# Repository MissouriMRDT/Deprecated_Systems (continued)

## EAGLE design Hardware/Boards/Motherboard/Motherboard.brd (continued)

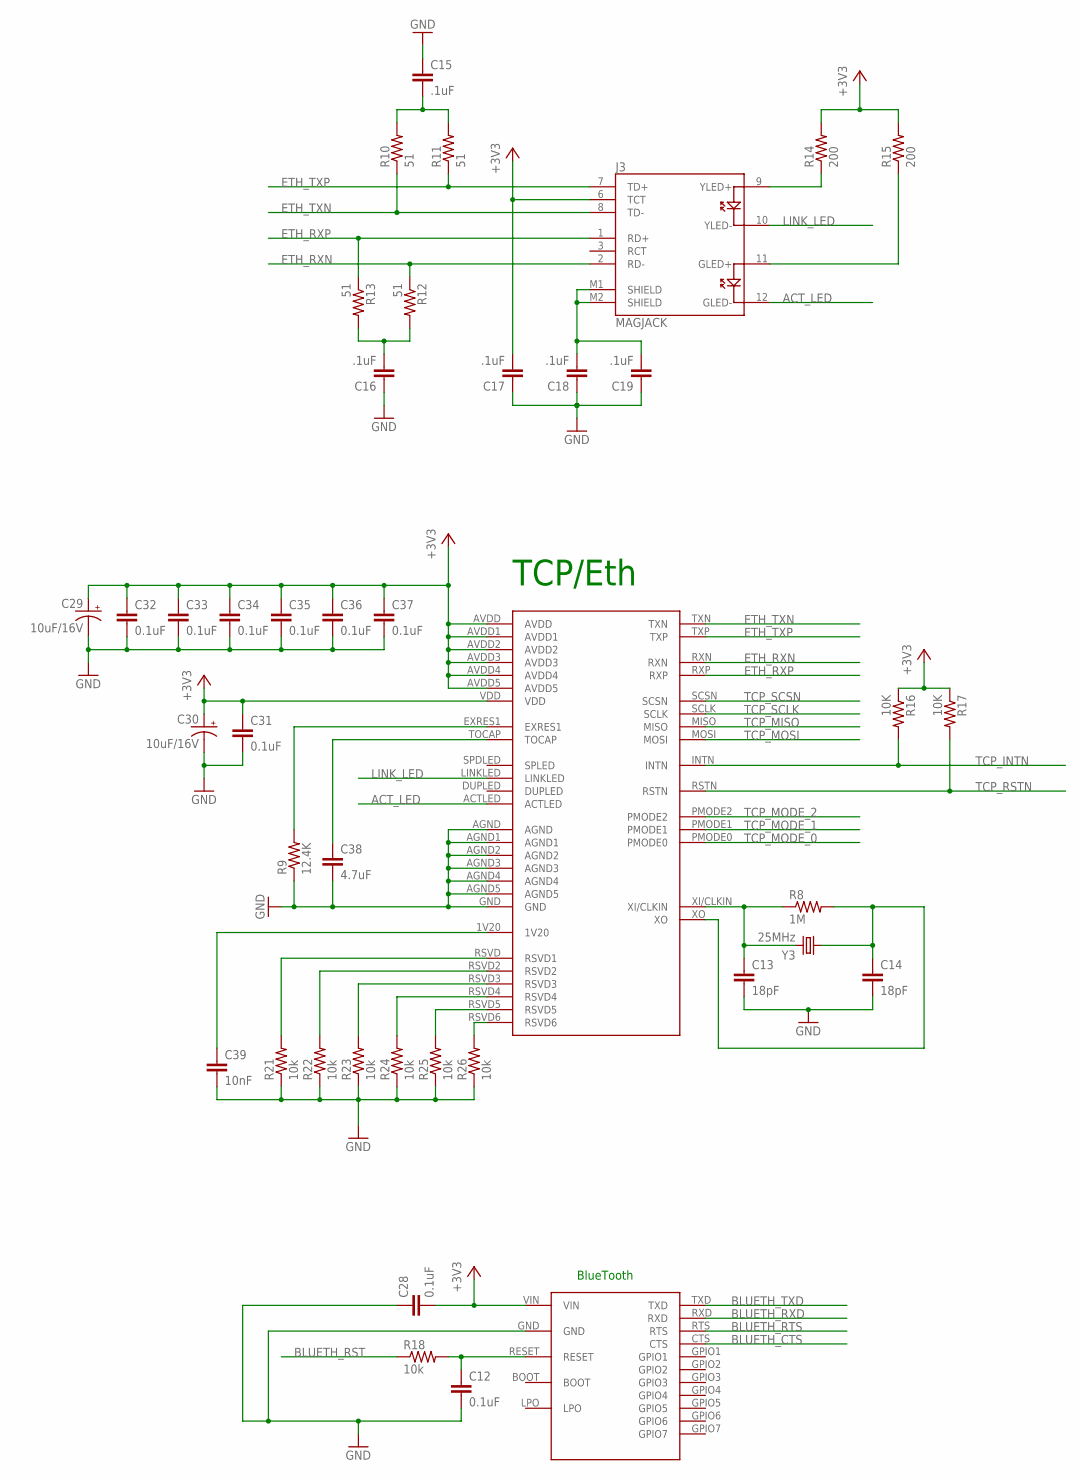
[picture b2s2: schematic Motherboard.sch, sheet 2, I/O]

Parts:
BLUETOOTH: SPBT2632C2A
C12, C28, C31, C32, C33, C34, C35, C36, C37: 0.1uF; 1206
C13, C14: 18pF; 1206
C15, C16, C17, C18, C19: .1uF; 1206
C29, C30: 10uF/16V; EIA3216
C38: 4.7uF; 1206
C39: 10nF; 1206
J3: MAGJACK
R8: 1M; 1206
R9: 12.4K; 1206
R10, R11, R12, R13: 51; 1206
R14, R15: 200; 1206
R16, R17: 10K; 1206
R18, R21, R22, R23, R24, R25, R26: 10k; 1206
U$11: W5500
Y3: 25MHz; HC49US

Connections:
+3V3: BLUETOOTH.VIN, C17.2, C28.2, C29.A (+), C30.A (+), C31.1, C32.1, C33.1, C34.1, C35.1, C36.1, C37.1, J3.6 (TCT), R14.2, R15.2, R16.1, R17.1, U$11.AVDD, U$11.AVDD1, U$11.AVDD2, U$11.AVDD3, U$11.AVDD4, U$11.AVDD5, U$11.VDD; also elsewhere on the board
ACT_LED: J3.12 (GLED-), U$11.ACTLED
BLUETH_CTS: BLUETOOTH.CTS; also elsewhere on the board
BLUETH_RST: R18.1; also elsewhere on the board
BLUETH_RTS: BLUETOOTH.RTS; also elsewhere on the board
BLUETH_RXD: BLUETOOTH.RXD; also elsewhere on the board
BLUETH_TXD: BLUETOOTH.TXD; also elsewhere on the board
ETH_RXN: J3.2 (RD-), R12.1, U$11.RXN
ETH_RXP: J3.1 (RD+), R13.1, U$11.RXP
ETH_TXN: J3.8 (TD-), R10.1, U$11.TXN
ETH_TXP: J3.7 (TD+), R11.1, U$11.TXP
GND: BLUETOOTH.GND, C12.2, C13.2, C14.2, C15.1, C16.1, C17.1, C18.1, C19.1, C28.1, C29.C (-), C30.C (-), C31.2, C32.2, C33.2, C34.2, C35.2, C36.2, C37.2, C38.2, C39.2, R9.1, R21.1, R22.1, R23.1, R24.1, R25.1, R26.1, U$11.AGND, U$11.AGND1, U$11.AGND2, U$11.AGND3, U$11.AGND4, U$11.AGND5, U$11.GND; also elsewhere on the board
LINK_LED: J3.10 (YLED-), U$11.LINKLED
unnamed: C13.1, R8.1, U$11.XI/CLKIN, Y3.2
unnamed: R9.2, U$11.EXRES1
unnamed: C14.1, R8.2, U$11.XO, Y3.1
unnamed: C15.2, R10.2, R11.2
unnamed: C16.2, R12.2, R13.2
unnamed: J3.9 (YLED+), R14.1
unnamed: C18.2, C19.2, J3.M1 (SHIELD), J3.M2 (SHIELD)
unnamed: J3.11 (GLED+), R15.1
unnamed: C38.1, U$11.TOCAP
unnamed: R26.2, U$11.RSVD6
unnamed: R25.2, U$11.RSVD5
unnamed: R24.2, U$11.RSVD4
unnamed: R23.2, U$11.RSVD3
unnamed: R22.2, U$11.RSVD2
unnamed: R21.2, U$11.RSVD (RSVD1)
unnamed: C39.1, U$11.1V20
unnamed: BLUETOOTH.RESET, C12.1, R18.2
TCP_INTN: R16.2, U$11.INTN; also elsewhere on the board
TCP_MISO: U$11.MISO; also elsewhere on the board
TCP_MODE_0: U$11.PMODE0; also elsewhere on the board
TCP_MODE_1: U$11.PMODE1; also elsewhere on the board
TCP_MODE_2: U$11.PMODE2; also elsewhere on the board
TCP_MOSI: U$11.MOSI; also elsewhere on the board
TCP_RSTN: R17.2, U$11.RSTN; also elsewhere on the board
TCP_SCLK: U$11.SCLK; also elsewhere on the board
TCP_SCSN: U$11.SCSN; also elsewhere on the board

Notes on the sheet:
TCP/Eth
BlueTooth

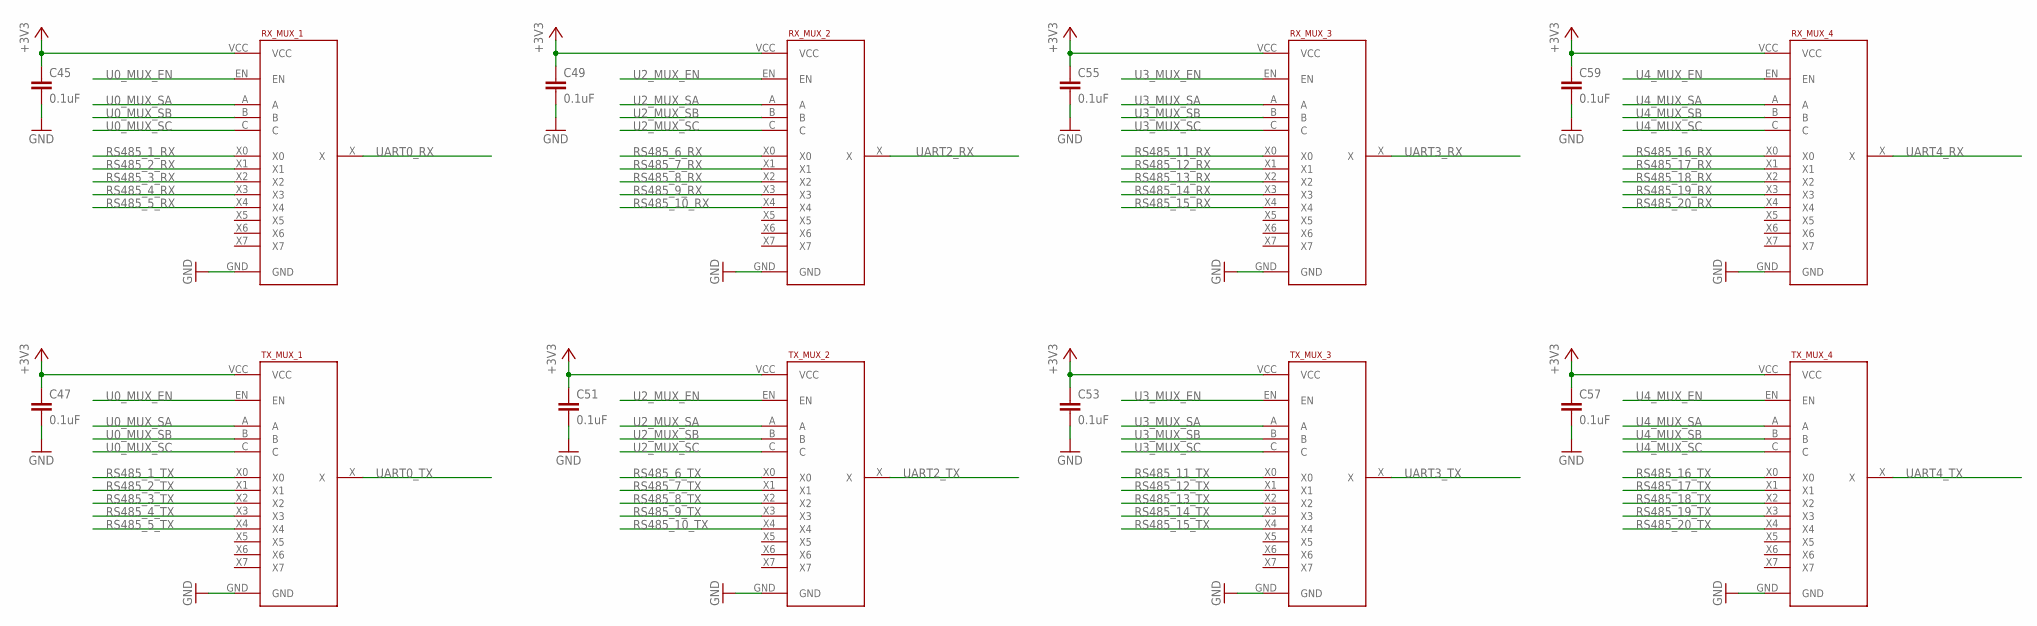
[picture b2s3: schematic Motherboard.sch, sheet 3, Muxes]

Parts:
C45, C47, C49, C51, C53, C55, C57, C59: 0.1uF; 1206
RX_MUX_1, RX_MUX_2, RX_MUX_3, RX_MUX_4: 8:1 Mux; SOIC16N
TX_MUX_1, TX_MUX_2, TX_MUX_3, TX_MUX_4: 8:1 Mux; SOIC16N

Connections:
+3V3: C45.1, C47.1, C49.1, C51.1, C53.1, C55.1, C57.1, C59.1, RX_MUX_1.VCC, RX_MUX_2.VCC, RX_MUX_3.VCC, RX_MUX_4.VCC, TX_MUX_1.VCC, TX_MUX_2.VCC, TX_MUX_3.VCC, TX_MUX_4.VCC; also elsewhere on the board
GND: C45.2, C47.2, C49.2, C51.2, C53.2, C55.2, C57.2, C59.2, RX_MUX_1.GND, RX_MUX_2.GND, RX_MUX_3.GND, RX_MUX_4.GND, TX_MUX_1.GND, TX_MUX_2.GND, TX_MUX_3.GND, TX_MUX_4.GND; also elsewhere on the board
RS485_1_RX: RX_MUX_1.X0; also elsewhere on the board
RS485_1_TX: TX_MUX_1.X0; also elsewhere on the board
RS485_2_RX: RX_MUX_1.X1; also elsewhere on the board
RS485_2_TX: TX_MUX_1.X1; also elsewhere on the board
RS485_3_RX: RX_MUX_1.X2; also elsewhere on the board
RS485_3_TX: TX_MUX_1.X2; also elsewhere on the board
RS485_4_RX: RX_MUX_1.X3; also elsewhere on the board
RS485_4_TX: TX_MUX_1.X3; also elsewhere on the board
RS485_5_RX: RX_MUX_1.X4; also elsewhere on the board
RS485_5_TX: TX_MUX_1.X4; also elsewhere on the board
RS485_6_RX: RX_MUX_2.X0; also elsewhere on the board
RS485_6_TX: TX_MUX_2.X0; also elsewhere on the board
RS485_7_RX: RX_MUX_2.X1; also elsewhere on the board
RS485_7_TX: TX_MUX_2.X1; also elsewhere on the board
RS485_8_RX: RX_MUX_2.X2; also elsewhere on the board
RS485_8_TX: TX_MUX_2.X2; also elsewhere on the board
RS485_9_RX: RX_MUX_2.X3; also elsewhere on the board
RS485_9_TX: TX_MUX_2.X3; also elsewhere on the board
RS485_10_RX: RX_MUX_2.X4; also elsewhere on the board
RS485_10_TX: TX_MUX_2.X4; also elsewhere on the board
RS485_11_RX: RX_MUX_3.X0; also elsewhere on the board
RS485_11_TX: TX_MUX_3.X0; also elsewhere on the board
RS485_12_RX: RX_MUX_3.X1; also elsewhere on the board
RS485_12_TX: TX_MUX_3.X1; also elsewhere on the board
RS485_13_RX: RX_MUX_3.X2; also elsewhere on the board
RS485_13_TX: TX_MUX_3.X2; also elsewhere on the board
RS485_14_RX: RX_MUX_3.X3; also elsewhere on the board
RS485_14_TX: TX_MUX_3.X3; also elsewhere on the board
RS485_15_RX: RX_MUX_3.X4; also elsewhere on the board
RS485_15_TX: TX_MUX_3.X4; also elsewhere on the board
RS485_16_RX: RX_MUX_4.X0; also elsewhere on the board
RS485_16_TX: TX_MUX_4.X0; also elsewhere on the board
RS485_17_RX: RX_MUX_4.X1; also elsewhere on the board
RS485_17_TX: TX_MUX_4.X1; also elsewhere on the board
RS485_18_RX: RX_MUX_4.X2; also elsewhere on the board
RS485_18_TX: TX_MUX_4.X2; also elsewhere on the board
RS485_19_RX: RX_MUX_4.X3; also elsewhere on the board
RS485_19_TX: TX_MUX_4.X3; also elsewhere on the board
RS485_20_RX: RX_MUX_4.X4; also elsewhere on the board
RS485_20_TX: TX_MUX_4.X4; also elsewhere on the board
U0_MUX_EN: RX_MUX_1.EN, TX_MUX_1.EN; also elsewhere on the board
U0_MUX_SA: RX_MUX_1.A, TX_MUX_1.A; also elsewhere on the board
U0_MUX_SB: RX_MUX_1.B, TX_MUX_1.B; also elsewhere on the board
U0_MUX_SC: RX_MUX_1.C, TX_MUX_1.C; also elsewhere on the board
U2_MUX_EN: RX_MUX_2.EN, TX_MUX_2.EN; also elsewhere on the board
U2_MUX_SA: RX_MUX_2.A, TX_MUX_2.A; also elsewhere on the board
U2_MUX_SB: RX_MUX_2.B, TX_MUX_2.B; also elsewhere on the board
U2_MUX_SC: RX_MUX_2.C, TX_MUX_2.C; also elsewhere on the board
U3_MUX_EN: RX_MUX_3.EN, TX_MUX_3.EN; also elsewhere on the board
U3_MUX_SA: RX_MUX_3.A, TX_MUX_3.A; also elsewhere on the board
U3_MUX_SB: RX_MUX_3.B, TX_MUX_3.B; also elsewhere on the board
U3_MUX_SC: RX_MUX_3.C, TX_MUX_3.C; also elsewhere on the board
U4_MUX_EN: RX_MUX_4.EN, TX_MUX_4.EN; also elsewhere on the board
U4_MUX_SA: RX_MUX_4.A, TX_MUX_4.A; also elsewhere on the board
U4_MUX_SB: RX_MUX_4.B, TX_MUX_4.B; also elsewhere on the board
U4_MUX_SC: RX_MUX_4.C, TX_MUX_4.C; also elsewhere on the board
UART0_RX: RX_MUX_1.X; also elsewhere on the board
UART0_TX: TX_MUX_1.X; also elsewhere on the board
UART2_RX: RX_MUX_2.X; also elsewhere on the board
UART2_TX: TX_MUX_2.X; also elsewhere on the board
UART3_RX: RX_MUX_3.X; also elsewhere on the board
UART3_TX: TX_MUX_3.X; also elsewhere on the board
UART4_RX: RX_MUX_4.X; also elsewhere on the board
UART4_TX: TX_MUX_4.X; also elsewhere on the board

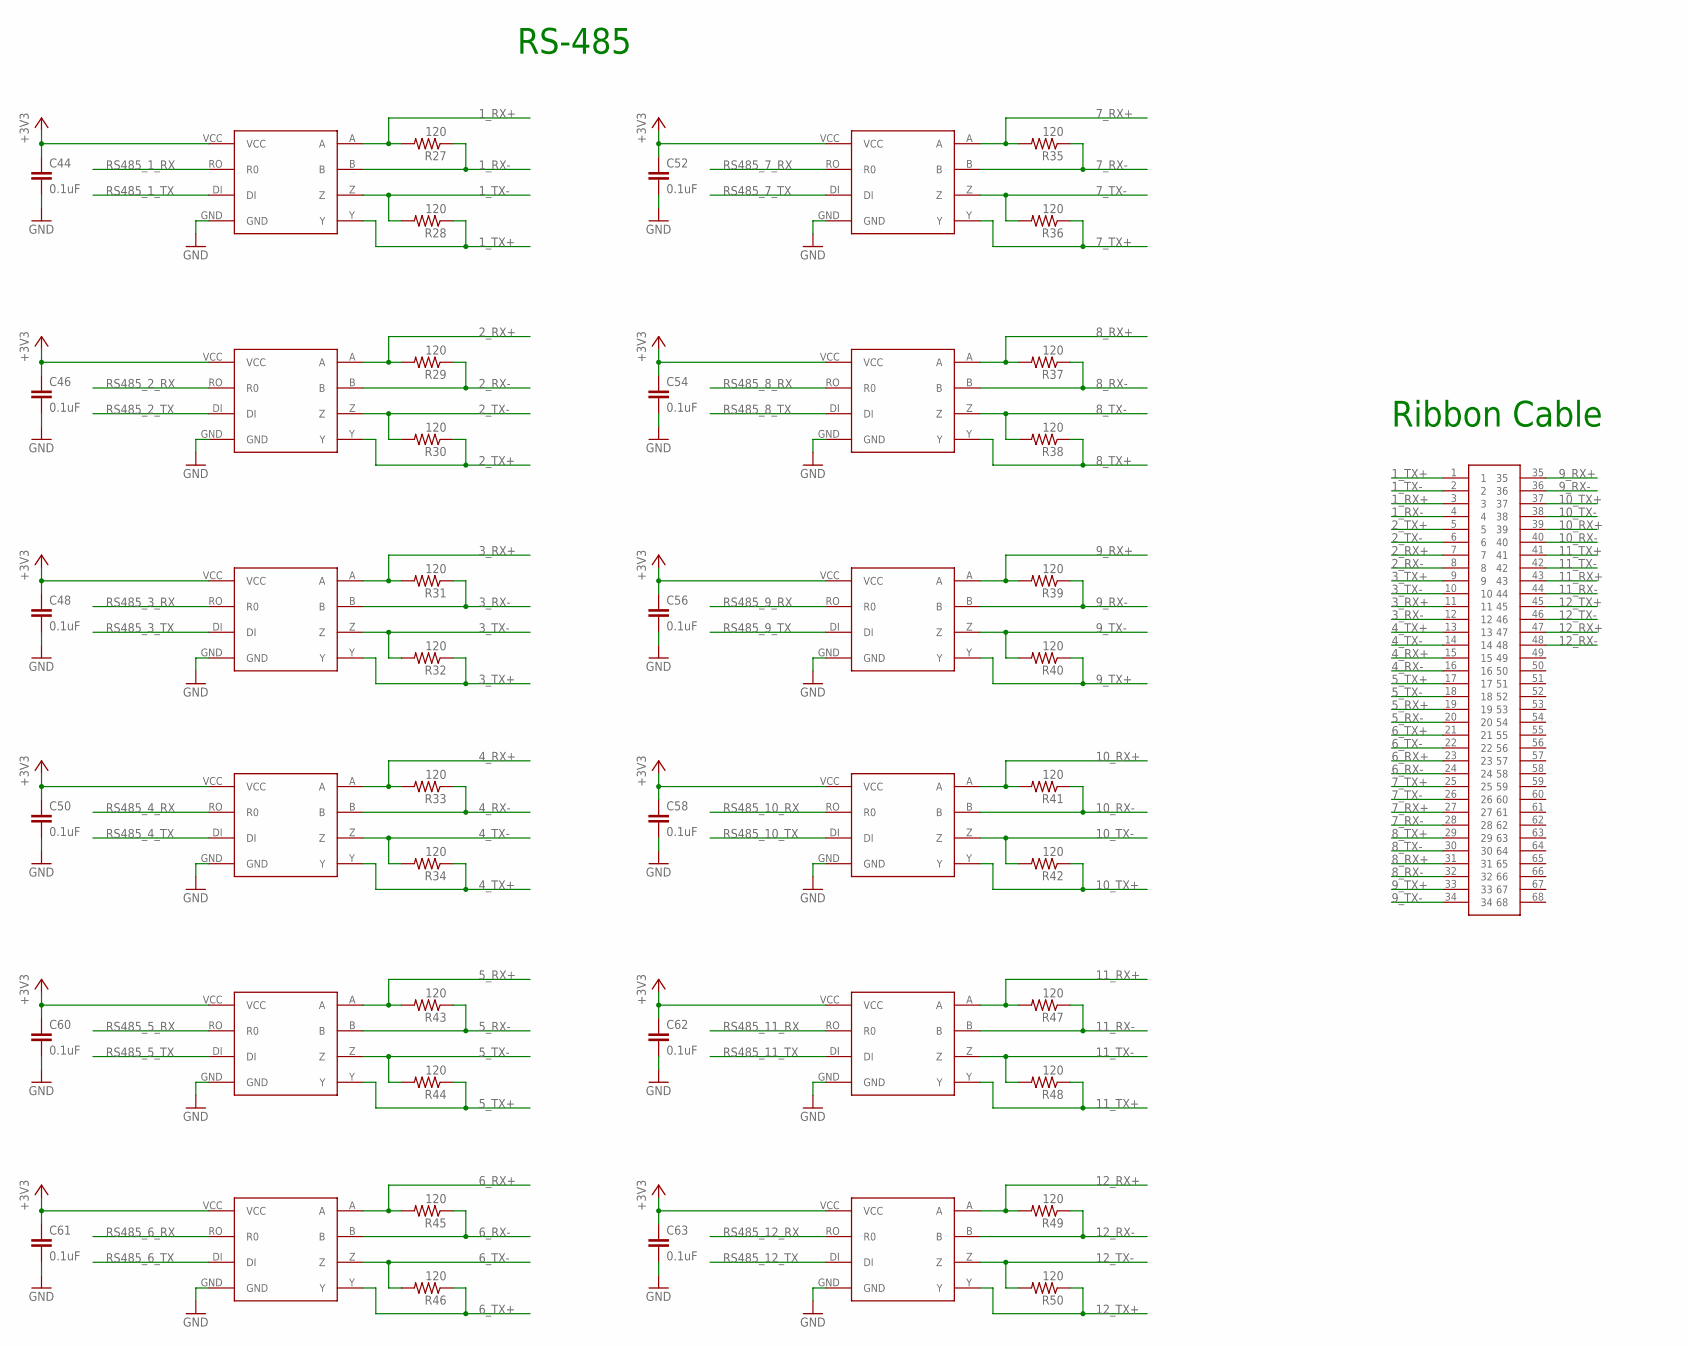
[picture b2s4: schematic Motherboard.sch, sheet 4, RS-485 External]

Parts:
C44, C46, C48, C50, C52, C54, C56, C58, C60, C61, C62, C63: 0.1uF; 1206
R27, R28, R29, R30, R31, R32, R33, R34, R35, R36, R37, R38, R39, R40, R41, R42, R43, R44, R45, R46, R47, R48, R49, R50: 120; 1206
RS_TRANS_1, RS_TRANS_2, RS_TRANS_3, RS_TRANS_4, RS_TRANS_5, RS_TRANS_6, RS_TRANS_7, RS_TRANS_8, RS_TRANS_9, RS_TRANS_10, RS_TRANS_11, RS_TRANS_12: MAX3077; MAX3070E
U$36: TB60050685100; 60050685100

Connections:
1_RX+: R27.2, RS_TRANS_1.A, U$36.3
1_RX-: R27.1, RS_TRANS_1.B, U$36.4
1_TX+: R28.1, RS_TRANS_1.Y, U$36.1
1_TX-: R28.2, RS_TRANS_1.Z, U$36.2
2_RX+: R29.2, RS_TRANS_2.A, U$36.7
2_RX-: R29.1, RS_TRANS_2.B, U$36.8
2_TX+: R30.1, RS_TRANS_2.Y, U$36.5
2_TX-: R30.2, RS_TRANS_2.Z, U$36.6
3_RX+: R31.2, RS_TRANS_3.A, U$36.11
3_RX-: R31.1, RS_TRANS_3.B, U$36.12
3_TX+: R32.1, RS_TRANS_3.Y, U$36.9
3_TX-: R32.2, RS_TRANS_3.Z, U$36.10
4_RX+: R33.2, RS_TRANS_4.A, U$36.15
4_RX-: R33.1, RS_TRANS_4.B, U$36.16
4_TX+: R34.1, RS_TRANS_4.Y, U$36.13
4_TX-: R34.2, RS_TRANS_4.Z, U$36.14
5_RX+: R43.2, RS_TRANS_9.A, U$36.19
5_RX-: R43.1, RS_TRANS_9.B, U$36.20
5_TX+: R44.1, RS_TRANS_9.Y, U$36.17
5_TX-: R44.2, RS_TRANS_9.Z, U$36.18
6_RX+: R45.2, RS_TRANS_10.A, U$36.23
6_RX-: R45.1, RS_TRANS_10.B, U$36.24
6_TX+: R46.1, RS_TRANS_10.Y, U$36.21
6_TX-: R46.2, RS_TRANS_10.Z, U$36.22
7_RX+: R35.2, RS_TRANS_5.A, U$36.27
7_RX-: R35.1, RS_TRANS_5.B, U$36.28
7_TX+: R36.1, RS_TRANS_5.Y, U$36.25
7_TX-: R36.2, RS_TRANS_5.Z, U$36.26
8_RX+: R37.2, RS_TRANS_6.A, U$36.31
8_RX-: R37.1, RS_TRANS_6.B, U$36.32
8_TX+: R38.1, RS_TRANS_6.Y, U$36.29
8_TX-: R38.2, RS_TRANS_6.Z, U$36.30
9_RX+: R39.2, RS_TRANS_7.A, U$36.35
9_RX-: R39.1, RS_TRANS_7.B, U$36.36
9_TX+: R40.1, RS_TRANS_7.Y, U$36.33
9_TX-: R40.2, RS_TRANS_7.Z, U$36.34
10_RX+: R41.2, RS_TRANS_8.A, U$36.39
10_RX-: R41.1, RS_TRANS_8.B, U$36.40
10_TX+: R42.1, RS_TRANS_8.Y, U$36.37
10_TX-: R42.2, RS_TRANS_8.Z, U$36.38
11_RX+: R47.2, RS_TRANS_11.A, U$36.43
11_RX-: R47.1, RS_TRANS_11.B, U$36.44
11_TX+: R48.1, RS_TRANS_11.Y, U$36.41
11_TX-: R48.2, RS_TRANS_11.Z, U$36.42
12_RX+: R49.2, RS_TRANS_12.A, U$36.47
12_RX-: R49.1, RS_TRANS_12.B, U$36.48
12_TX+: R50.1, RS_TRANS_12.Y, U$36.45
12_TX-: R50.2, RS_TRANS_12.Z, U$36.46
+3V3: C44.1, C46.1, C48.1, C50.1, C52.1, C54.1, C56.1, C58.1, C60.1, C61.1, C62.1, C63.1, RS_TRANS_1.VCC, RS_TRANS_2.VCC, RS_TRANS_3.VCC, RS_TRANS_4.VCC, RS_TRANS_5.VCC, RS_TRANS_6.VCC, RS_TRANS_7.VCC, RS_TRANS_8.VCC, RS_TRANS_9.VCC, RS_TRANS_10.VCC, RS_TRANS_11.VCC, RS_TRANS_12.VCC; also elsewhere on the board
GND: C44.2, C46.2, C48.2, C50.2, C52.2, C54.2, C56.2, C58.2, C60.2, C61.2, C62.2, C63.2, RS_TRANS_1.GND, RS_TRANS_2.GND, RS_TRANS_3.GND, RS_TRANS_4.GND, RS_TRANS_5.GND, RS_TRANS_6.GND, RS_TRANS_7.GND, RS_TRANS_8.GND, RS_TRANS_9.GND, RS_TRANS_10.GND, RS_TRANS_11.GND, RS_TRANS_12.GND; also elsewhere on the board
RS485_1_RX: RS_TRANS_1.RO (R0); also elsewhere on the board
RS485_1_TX: RS_TRANS_1.DI; also elsewhere on the board
RS485_2_RX: RS_TRANS_2.RO (R0); also elsewhere on the board
RS485_2_TX: RS_TRANS_2.DI; also elsewhere on the board
RS485_3_RX: RS_TRANS_3.RO (R0); also elsewhere on the board
RS485_3_TX: RS_TRANS_3.DI; also elsewhere on the board
RS485_4_RX: RS_TRANS_4.RO (R0); also elsewhere on the board
RS485_4_TX: RS_TRANS_4.DI; also elsewhere on the board
RS485_5_RX: RS_TRANS_9.RO (R0); also elsewhere on the board
RS485_5_TX: RS_TRANS_9.DI; also elsewhere on the board
RS485_6_RX: RS_TRANS_10.RO (R0); also elsewhere on the board
RS485_6_TX: RS_TRANS_10.DI; also elsewhere on the board
RS485_7_RX: RS_TRANS_5.RO (R0); also elsewhere on the board
RS485_7_TX: RS_TRANS_5.DI; also elsewhere on the board
RS485_8_RX: RS_TRANS_6.RO (R0); also elsewhere on the board
RS485_8_TX: RS_TRANS_6.DI; also elsewhere on the board
RS485_9_RX: RS_TRANS_7.RO (R0); also elsewhere on the board
RS485_9_TX: RS_TRANS_7.DI; also elsewhere on the board
RS485_10_RX: RS_TRANS_8.RO (R0); also elsewhere on the board
RS485_10_TX: RS_TRANS_8.DI; also elsewhere on the board
RS485_11_RX: RS_TRANS_11.RO (R0); also elsewhere on the board
RS485_11_TX: RS_TRANS_11.DI; also elsewhere on the board
RS485_12_RX: RS_TRANS_12.RO (R0); also elsewhere on the board
RS485_12_TX: RS_TRANS_12.DI; also elsewhere on the board

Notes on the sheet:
Ribbon Cable
RS-485

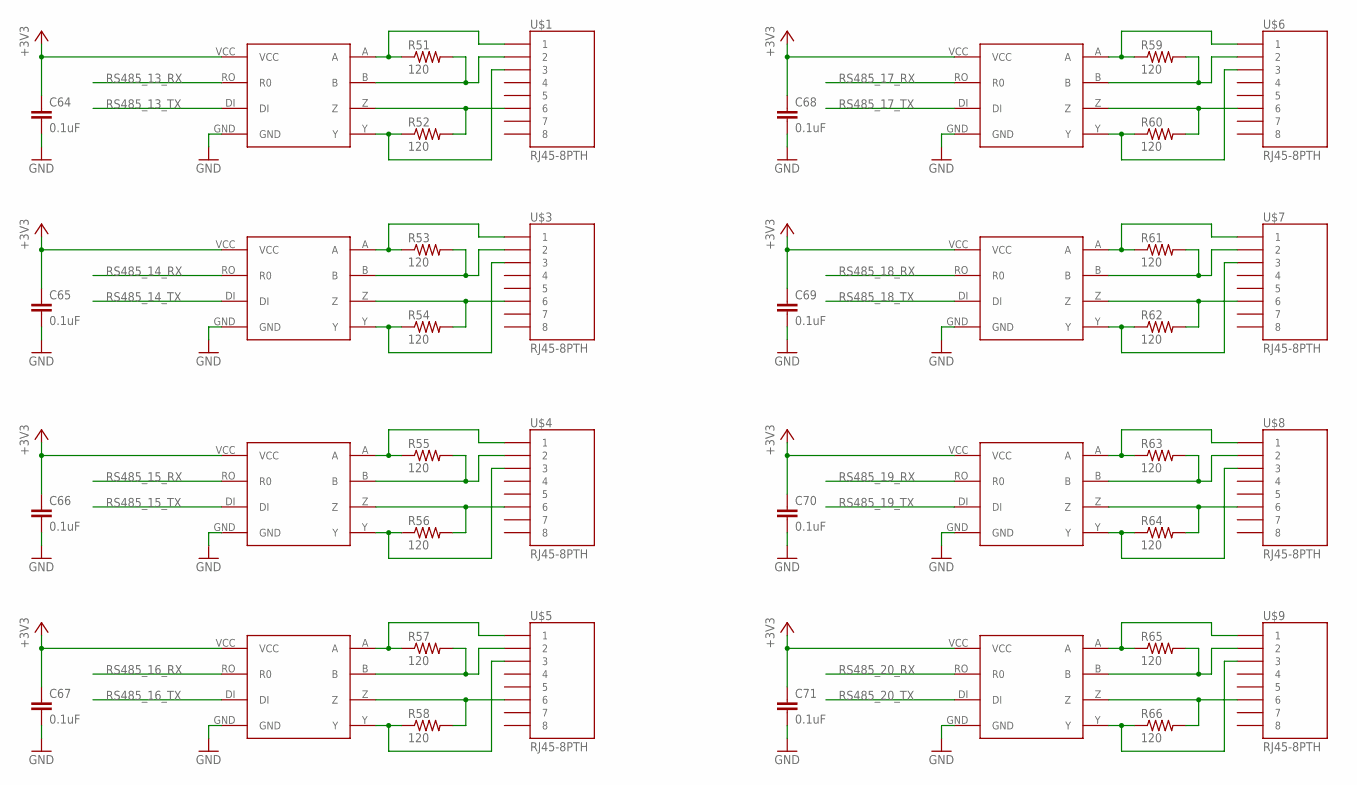
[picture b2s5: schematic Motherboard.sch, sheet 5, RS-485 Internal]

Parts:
C64, C65, C66, C67, C68, C69, C70, C71: 0.1uF; 1206
R51, R52, R53, R54, R55, R56, R57, R58, R59, R60, R61, R62, R63, R64, R65, R66: 120; 1206
RS-485-1, RS-485-2, RS-485-3, RS-485-4, RS-485-5, RS-485-6, RS-485-7, RS-485-8: MAX3077; MAX3070E
U$1, U$3, U$4, U$5, U$6, U$7, U$8, U$9: RJ45-8PTH; RJ45-8

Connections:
+3V3: C64.1, C65.1, C66.1, C67.1, C68.1, C69.1, C70.1, C71.1, RS-485-1.VCC, RS-485-2.VCC, RS-485-3.VCC, RS-485-4.VCC, RS-485-5.VCC, RS-485-6.VCC, RS-485-7.VCC, RS-485-8.VCC; also elsewhere on the board
GND: C64.2, C65.2, C66.2, C67.2, C68.2, C69.2, C70.2, C71.2, RS-485-1.GND, RS-485-2.GND, RS-485-3.GND, RS-485-4.GND, RS-485-5.GND, RS-485-6.GND, RS-485-7.GND, RS-485-8.GND; also elsewhere on the board
unnamed: R51.1, RS-485-1.A, U$1.1
unnamed: R51.2, RS-485-1.B, U$1.2
unnamed: R52.1, RS-485-1.Y, U$1.3
unnamed: R54.2, RS-485-2.Z, U$3.6
unnamed: R52.2, RS-485-1.Z, U$1.6
unnamed: R53.1, RS-485-2.A, U$3.1
unnamed: R53.2, RS-485-2.B, U$3.2
unnamed: R54.1, RS-485-2.Y, U$3.3
unnamed: R56.2, RS-485-3.Z, U$4.6
unnamed: R55.1, RS-485-3.A, U$4.1
unnamed: R55.2, RS-485-3.B, U$4.2
unnamed: R56.1, RS-485-3.Y, U$4.3
unnamed: R58.2, RS-485-4.Z, U$5.6
unnamed: R57.1, RS-485-4.A, U$5.1
unnamed: R57.2, RS-485-4.B, U$5.2
unnamed: R58.1, RS-485-4.Y, U$5.3
unnamed: R60.2, RS-485-5.Z, U$6.6
unnamed: R59.1, RS-485-5.A, U$6.1
unnamed: R59.2, RS-485-5.B, U$6.2
unnamed: R60.1, RS-485-5.Y, U$6.3
unnamed: R62.2, RS-485-6.Z, U$7.6
unnamed: R61.1, RS-485-6.A, U$7.1
unnamed: R61.2, RS-485-6.B, U$7.2
unnamed: R62.1, RS-485-6.Y, U$7.3
unnamed: R64.2, RS-485-7.Z, U$8.6
unnamed: R63.1, RS-485-7.A, U$8.1
unnamed: R63.2, RS-485-7.B, U$8.2
unnamed: R64.1, RS-485-7.Y, U$8.3
unnamed: R66.2, RS-485-8.Z, U$9.6
unnamed: R65.1, RS-485-8.A, U$9.1
unnamed: R65.2, RS-485-8.B, U$9.2
unnamed: R66.1, RS-485-8.Y, U$9.3
RS485_13_RX: RS-485-1.RO (R0); also elsewhere on the board
RS485_13_TX: RS-485-1.DI; also elsewhere on the board
RS485_14_RX: RS-485-2.RO (R0); also elsewhere on the board
RS485_14_TX: RS-485-2.DI; also elsewhere on the board
RS485_15_RX: RS-485-3.RO (R0); also elsewhere on the board
RS485_15_TX: RS-485-3.DI; also elsewhere on the board
RS485_16_RX: RS-485-4.RO (R0); also elsewhere on the board
RS485_16_TX: RS-485-4.DI; also elsewhere on the board
RS485_17_RX: RS-485-5.RO (R0); also elsewhere on the board
RS485_17_TX: RS-485-5.DI; also elsewhere on the board
RS485_18_RX: RS-485-6.RO (R0); also elsewhere on the board
RS485_18_TX: RS-485-6.DI; also elsewhere on the board
RS485_19_RX: RS-485-7.RO (R0); also elsewhere on the board
RS485_19_TX: RS-485-7.DI; also elsewhere on the board
RS485_20_RX: RS-485-8.RO (R0); also elsewhere on the board
RS485_20_TX: RS-485-8.DI; also elsewhere on the board

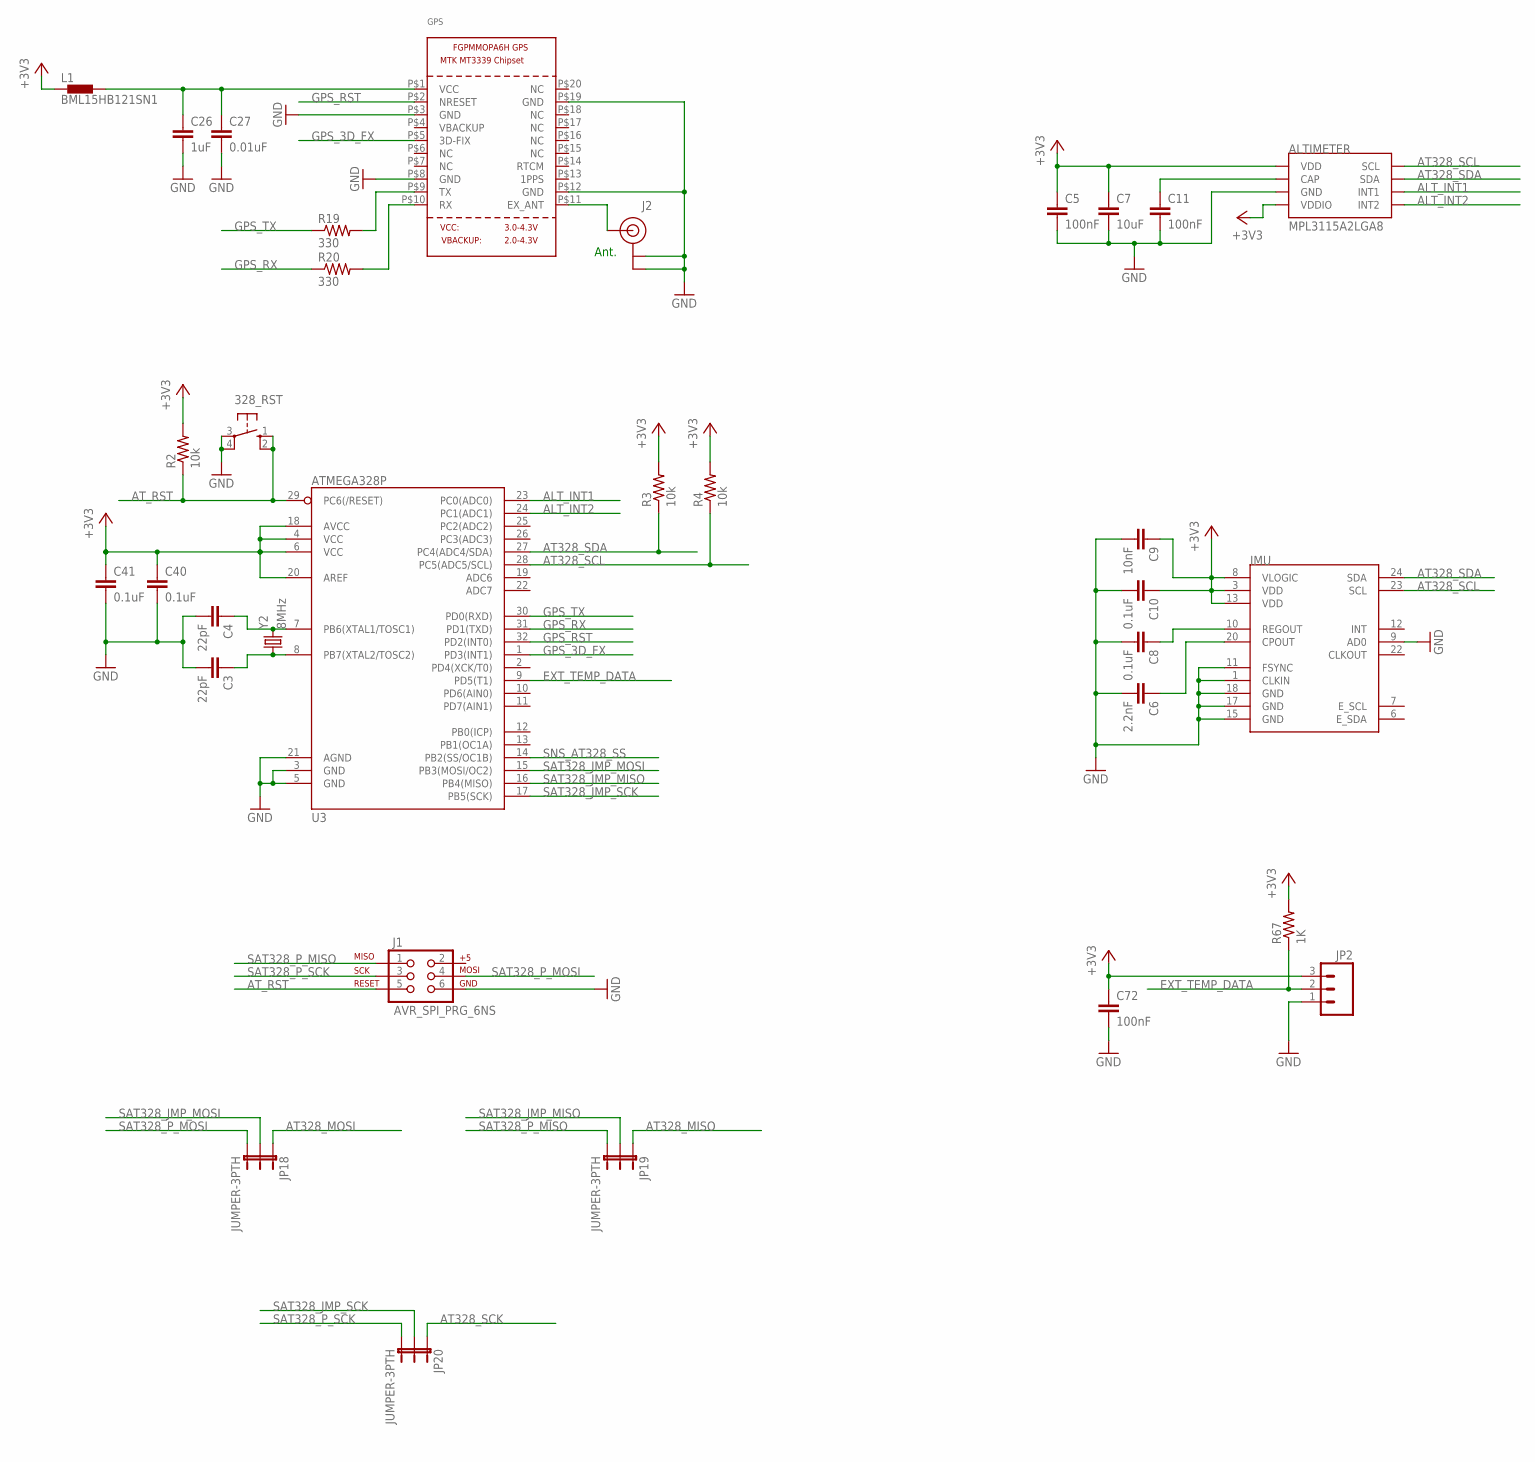
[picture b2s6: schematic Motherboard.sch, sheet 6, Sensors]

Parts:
328_RST: 10-XX; B3F-10XX
ALTIMETER: MPL3115A2LGA8; LGA8
C3, C4: 22pF; 1206
C5, C11, C72: 100nF; 1206
C6: 2.2nF; 1206
C7: 10uF; 1206
C8, C10, C40, C41: 0.1uF; 1206
C9: 10nF; 1206
C26: 1uF; 1206
C27: 0.01uF; 1206
GPS: GPS_FGPMMOPA6H; FGPMMOPA6H
IMU: MPU-9150QFN-24-NP; QFN-24-NP
J1: AVR_SPI_PRG_6NS; 2X3-NS
J2: U.FL
JP2: M03PTH; 1X03
JP18, JP19, JP20: JUMPER-3PTH; 1X03
L1: BML15HB121SN1; 0402
R2, R3, R4: 10k; 1206
R19, R20: 330; 1206
R67: 1K; 1206
U3: ATMEGA328P; TQFP32-08
Y2: 8MHz; HC49US

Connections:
+3V3: ALTIMETER.1 (VDD), ALTIMETER.4 (VDDIO), C5.1, C7.1, C9.1, C10.1, C40.1, C41.1, C72.1, IMU.3 (VDD), IMU.8 (VLOGIC), IMU.13 (VDD), JP2.3, L1.1, R2.2, R3.2, R4.2, R67.2, U3.4 (VCC), U3.6 (VCC), U3.18 (AVCC), U3.20 (AREF); also elsewhere on the board
ALT_INT1: ALTIMETER.6 (INT1), U3.23 (PC0(ADC0))
ALT_INT2: ALTIMETER.5 (INT2), U3.24 (PC1(ADC1))
AT328_MISO: JP19.1; also elsewhere on the board
AT328_MOSI: JP18.1; also elsewhere on the board
AT328_SCK: JP20.1; also elsewhere on the board
AT328_SCL: ALTIMETER.8 (SCL), IMU.23 (SCL), R4.1, U3.28 (PC5(ADC5/SCL))
AT328_SDA: ALTIMETER.7 (SDA), IMU.24 (SDA), R3.1, U3.27 (PC4(ADC4/SDA))
ATCLK1: C4.1, U3.7 (PB6(XTAL1/TOSC1)), Y2.2
ATCLK2: C3.1, U3.8 (PB7(XTAL2/TOSC2)), Y2.1
AT_RST: 328_RST.1 (S), 328_RST.2 (S1), J1.5, R2.1, U3.29 (PC6(/RESET)); also elsewhere on the board
EXT_TEMP_DATA: JP2.2, R67.1, U3.9 (PD5(T1))
GND: 328_RST.3, 328_RST.4 (P1), ALTIMETER.3 (GND), C3.2, C4.2, C5.2, C6.2, C7.2, C8.2, C9.2, C10.2, C11.2, C26.2, C27.2, C40.2, C41.2, C72.2, GPS.P$3 (GND), GPS.P$8 (GND), GPS.P$12 (GND), GPS.P$19 (GND), IMU.1 (CLKIN), IMU.9 (AD0), IMU.11 (FSYNC), IMU.15 (GND), IMU.17 (GND), IMU.18 (GND), J1.6, J2.P$1 (GND), J2.P$2 (GND), JP2.1, U3.3 (GND), U3.5 (GND), U3.21 (AGND); also elsewhere on the board
GPS_3D_FX: GPS.P$5 (3D-FIX), U3.1 (PD3(INT1))
GPS_RST: GPS.P$2 (NRESET), U3.32 (PD2(INT0))
GPS_RX: R20.1, U3.31 (PD1(TXD))
GPS_TX: R19.1, U3.30 (PD0(RXD))
unnamed: GPS.P$11 (EX_ANT), J2.P$3 (SIGNAL)
unnamed: C6.1, IMU.20 (CPOUT)
unnamed: C8.1, IMU.10 (REGOUT)
unnamed: ALTIMETER.2 (CAP), C11.1
unnamed: C26.1, C27.1, GPS.P$1 (VCC), L1.2
unnamed: GPS.P$9 (TX), R19.2
unnamed: GPS.P$10 (RX), R20.2
SAT328_JMP_MISO: JP19.2, U3.16 (PB4(MISO))
SAT328_JMP_MOSI: JP18.2, U3.15 (PB3(MOSI/OC2))
SAT328_JMP_SCK: JP20.2, U3.17 (PB5(SCK))
SAT328_P_MISO: J1.1, JP19.3
SAT328_P_MOSI: J1.4, JP18.3
SAT328_P_SCK: J1.3, JP20.3
SNS_AT328_SS: U3.14 (PB2(SS/OC1B)); also elsewhere on the board

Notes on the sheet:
Ant.

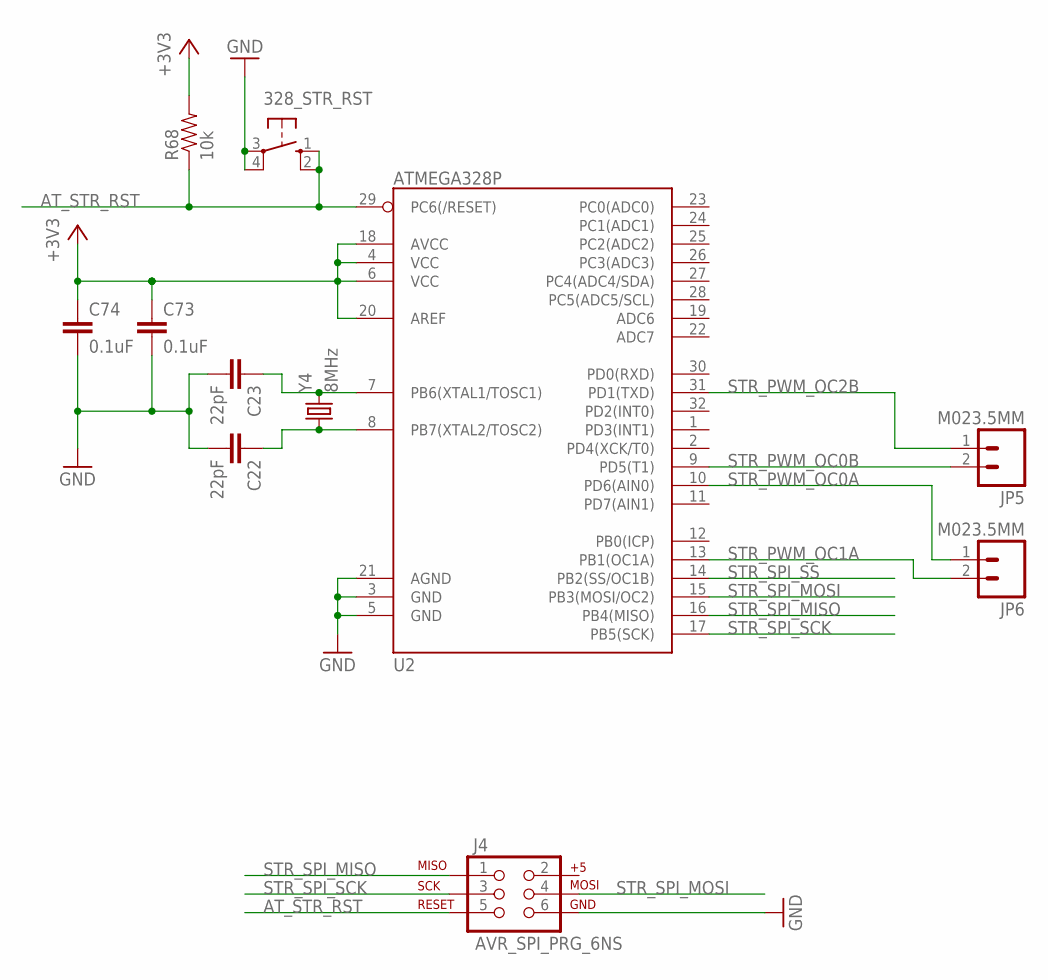
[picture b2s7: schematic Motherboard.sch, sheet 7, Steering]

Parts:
328_STR_RST: 10-XX; B3F-10XX
C22, C23: 22pF; 1206
C73, C74: 0.1uF; 1206
J4: AVR_SPI_PRG_6NS; 2X3-NS
JP5, JP6: M023.5MM; SCREWTERMINAL-3.5MM-2
R68: 10k; 1206
U2: ATMEGA328P; TQFP32-08
Y4: 8MHz; HC49US

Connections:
+3V3: C73.1, C74.1, R68.2, U2.4 (VCC), U2.6 (VCC), U2.18 (AVCC), U2.20 (AREF); also elsewhere on the board
ATCLK3: C22.1, U2.8 (PB7(XTAL2/TOSC2)), Y4.1
ATCLK4: C23.1, U2.7 (PB6(XTAL1/TOSC1)), Y4.2
AT_STR_RST: 328_STR_RST.1 (S), 328_STR_RST.2 (S1), J4.5, R68.1, U2.29 (PC6(/RESET)); also elsewhere on the board
GND: 328_STR_RST.3, 328_STR_RST.4 (P1), C22.2, C23.2, C73.2, C74.2, J4.6, U2.3 (GND), U2.5 (GND), U2.21 (AGND); also elsewhere on the board
STR_PWM_OC0A: JP6.1, U2.10 (PD6(AIN0))
STR_PWM_OC0B: JP5.2, U2.9 (PD5(T1))
STR_PWM_OC1A: JP6.2, U2.13 (PB1(OC1A))
STR_PWM_OC2B: JP5.1, U2.31 (PD1(TXD))
STR_SPI_MISO: J4.1, U2.16 (PB4(MISO)); also elsewhere on the board
STR_SPI_MOSI: J4.4, U2.15 (PB3(MOSI/OC2)); also elsewhere on the board
STR_SPI_SCK: J4.3, U2.17 (PB5(SCK)); also elsewhere on the board
STR_SPI_SS: U2.14 (PB2(SS/OC1B)); also elsewhere on the board

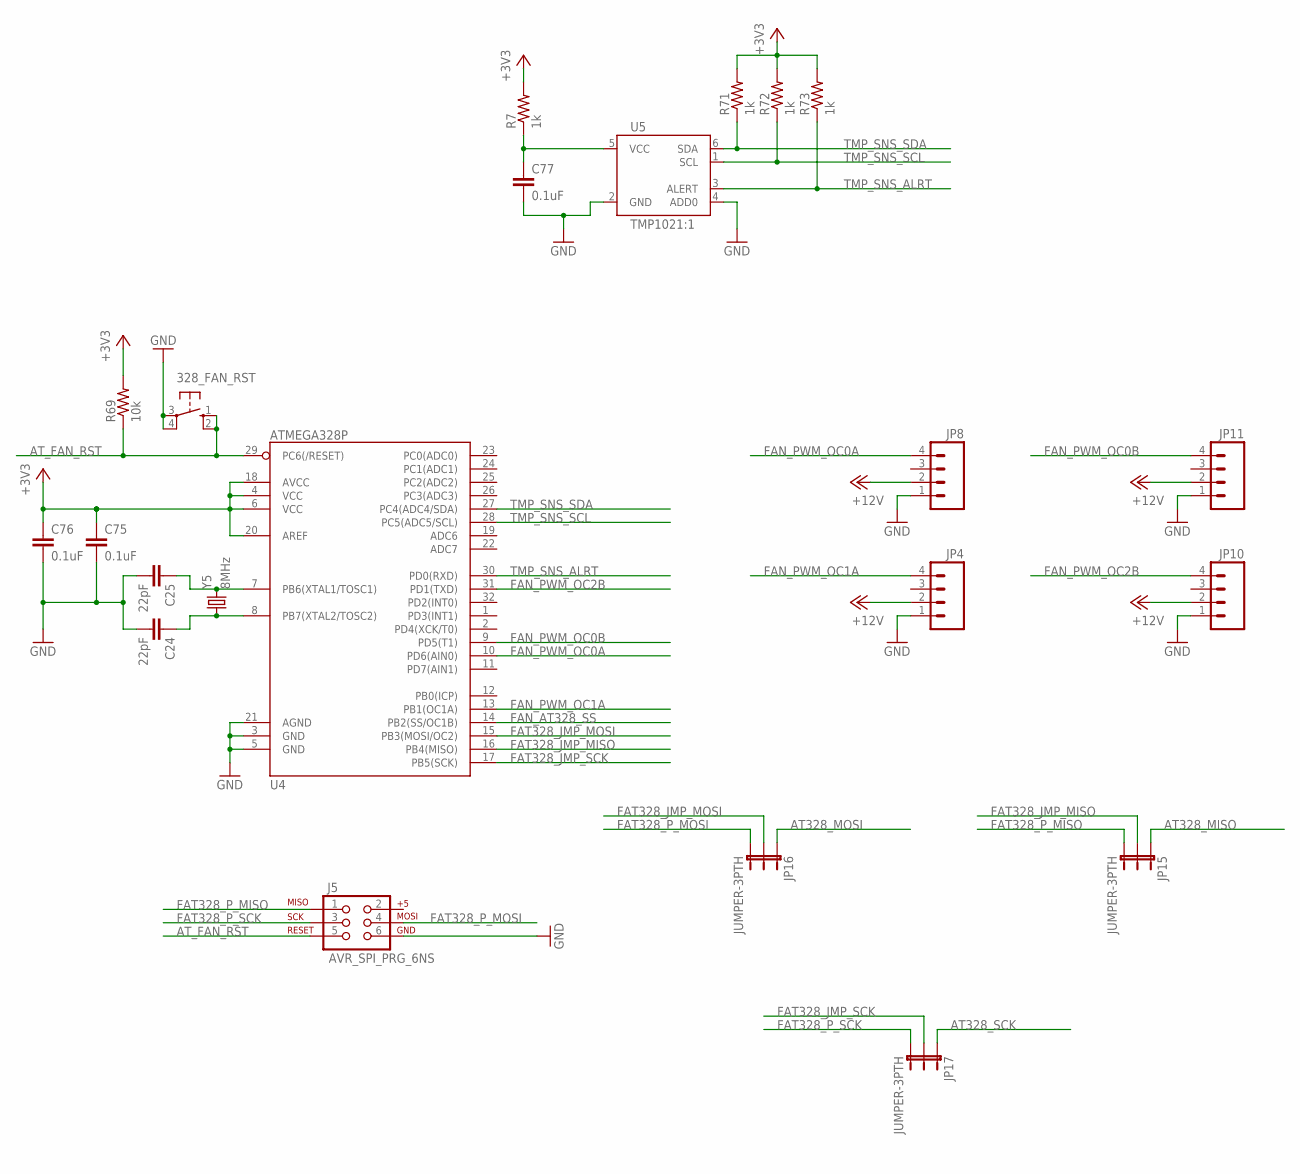
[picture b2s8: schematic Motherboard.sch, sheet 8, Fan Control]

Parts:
328_FAN_RST: 10-XX; B3F-10XX
C24, C25: 22pF; 1206
C75, C76, C77: 0.1uF; 1206
J5: AVR_SPI_PRG_6NS; 2X3-NS
JP4, JP8, JP10, JP11: M04POLAR; MOLEX-1X4
JP15, JP16, JP17: JUMPER-3PTH; 1X03
R7, R71, R72, R73: 1k; 1206
R69: 10k; 1206
U4: ATMEGA328P; TQFP32-08
U5: TMP1021:1; SOT563-2
Y5: 8MHz; HC49US

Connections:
+3V3: C75.1, C76.1, R7.2, R69.2, R71.2, R72.2, R73.2, U4.20 (AREF); also elsewhere on the board
+12V: JP4.2, JP8.2, JP10.2, JP11.2; also elsewhere on the board
AT328_MISO: JP15.1; also elsewhere on the board
AT328_MOSI: JP16.1; also elsewhere on the board
AT328_SCK: JP17.1; also elsewhere on the board
ATCLK5: C24.1, U4.8 (PB7(XTAL2/TOSC2)), Y5.1
ATCLK6: C25.1, U4.7 (PB6(XTAL1/TOSC1)), Y5.2
AT_FAN_RST: 328_FAN_RST.1 (S), 328_FAN_RST.2 (S1), J5.5, R69.1, U4.29 (PC6(/RESET)); also elsewhere on the board
FAN_AT328_SS: U4.14 (PB2(SS/OC1B)); also elsewhere on the board
FAN_PWM_OC0A: JP8.4, U4.10 (PD6(AIN0))
FAN_PWM_OC0B: JP11.4, U4.9 (PD5(T1))
FAN_PWM_OC1A: JP4.4, U4.13 (PB1(OC1A))
FAN_PWM_OC2B: JP10.4, U4.31 (PD1(TXD))
FAT328_JMP_MISO: JP15.2, U4.16 (PB4(MISO))
FAT328_JMP_MOSI: JP16.2, U4.15 (PB3(MOSI/OC2))
FAT328_JMP_SCK: JP17.2, U4.17 (PB5(SCK))
FAT328_P_MISO: J5.1, JP15.3
FAT328_P_MOSI: J5.4, JP16.3
FAT328_P_SCK: J5.3, JP17.3
GND: 328_FAN_RST.3, 328_FAN_RST.4 (P1), C24.2, C25.2, C75.2, C76.2, C77.2, J5.6, JP4.1, JP8.1, JP10.1, JP11.1, U4.3 (GND), U4.5 (GND), U4.21 (AGND), U5.2 (GND), U5.4 (ADD0); also elsewhere on the board
unnamed: C77.1, R7.1, U5.5 (VCC)
TMP_SNS_ALRT: R73.1, U4.30 (PD0(RXD)), U5.3 (ALERT)
TMP_SNS_SCL: R72.1, U4.28 (PC5(ADC5/SCL)), U5.1 (SCL)
TMP_SNS_SDA: R71.1, U4.27 (PC4(ADC4/SDA)), U5.6 (SDA)

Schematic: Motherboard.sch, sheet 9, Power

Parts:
C42: 100nF; 1206
C43: 10uF; 1206
D1, D2: GREEN; LED-1206
JP1, JP7: M025MM; SCREWTERMINAL-5MM-2
R5, R70: 330; 1206
U$2: LD1117; LD1117SOT-223

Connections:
+3V3: C43.1, R70.1, U$2.VOUT; also elsewhere on the board
+5V: C42.1, JP1.2, U$2.VIN
+12V: JP7.2, R5.1; also elsewhere on the board
GND: C42.2, C43.2, D1.C, D2.C, JP1.1, JP7.1, U$2.GND; also elsewhere on the board
unnamed: D1.A, R70.2
unnamed: D2.A, R5.2
